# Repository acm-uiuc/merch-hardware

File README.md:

# Hardware to make Merch function

All the designs for the hardware components of Merch are found here.

## Components

### Vending Machine

This machine is a Dixie Narco 5800 Bevmax **4**, **not a Bevmax 3 machine**.

### Merch Hat

This unofficial Raspberry-Pi Hat allows a Pi to emulate keypresses on the machine's keypad.

### iPad Mount

### Connection Pictures

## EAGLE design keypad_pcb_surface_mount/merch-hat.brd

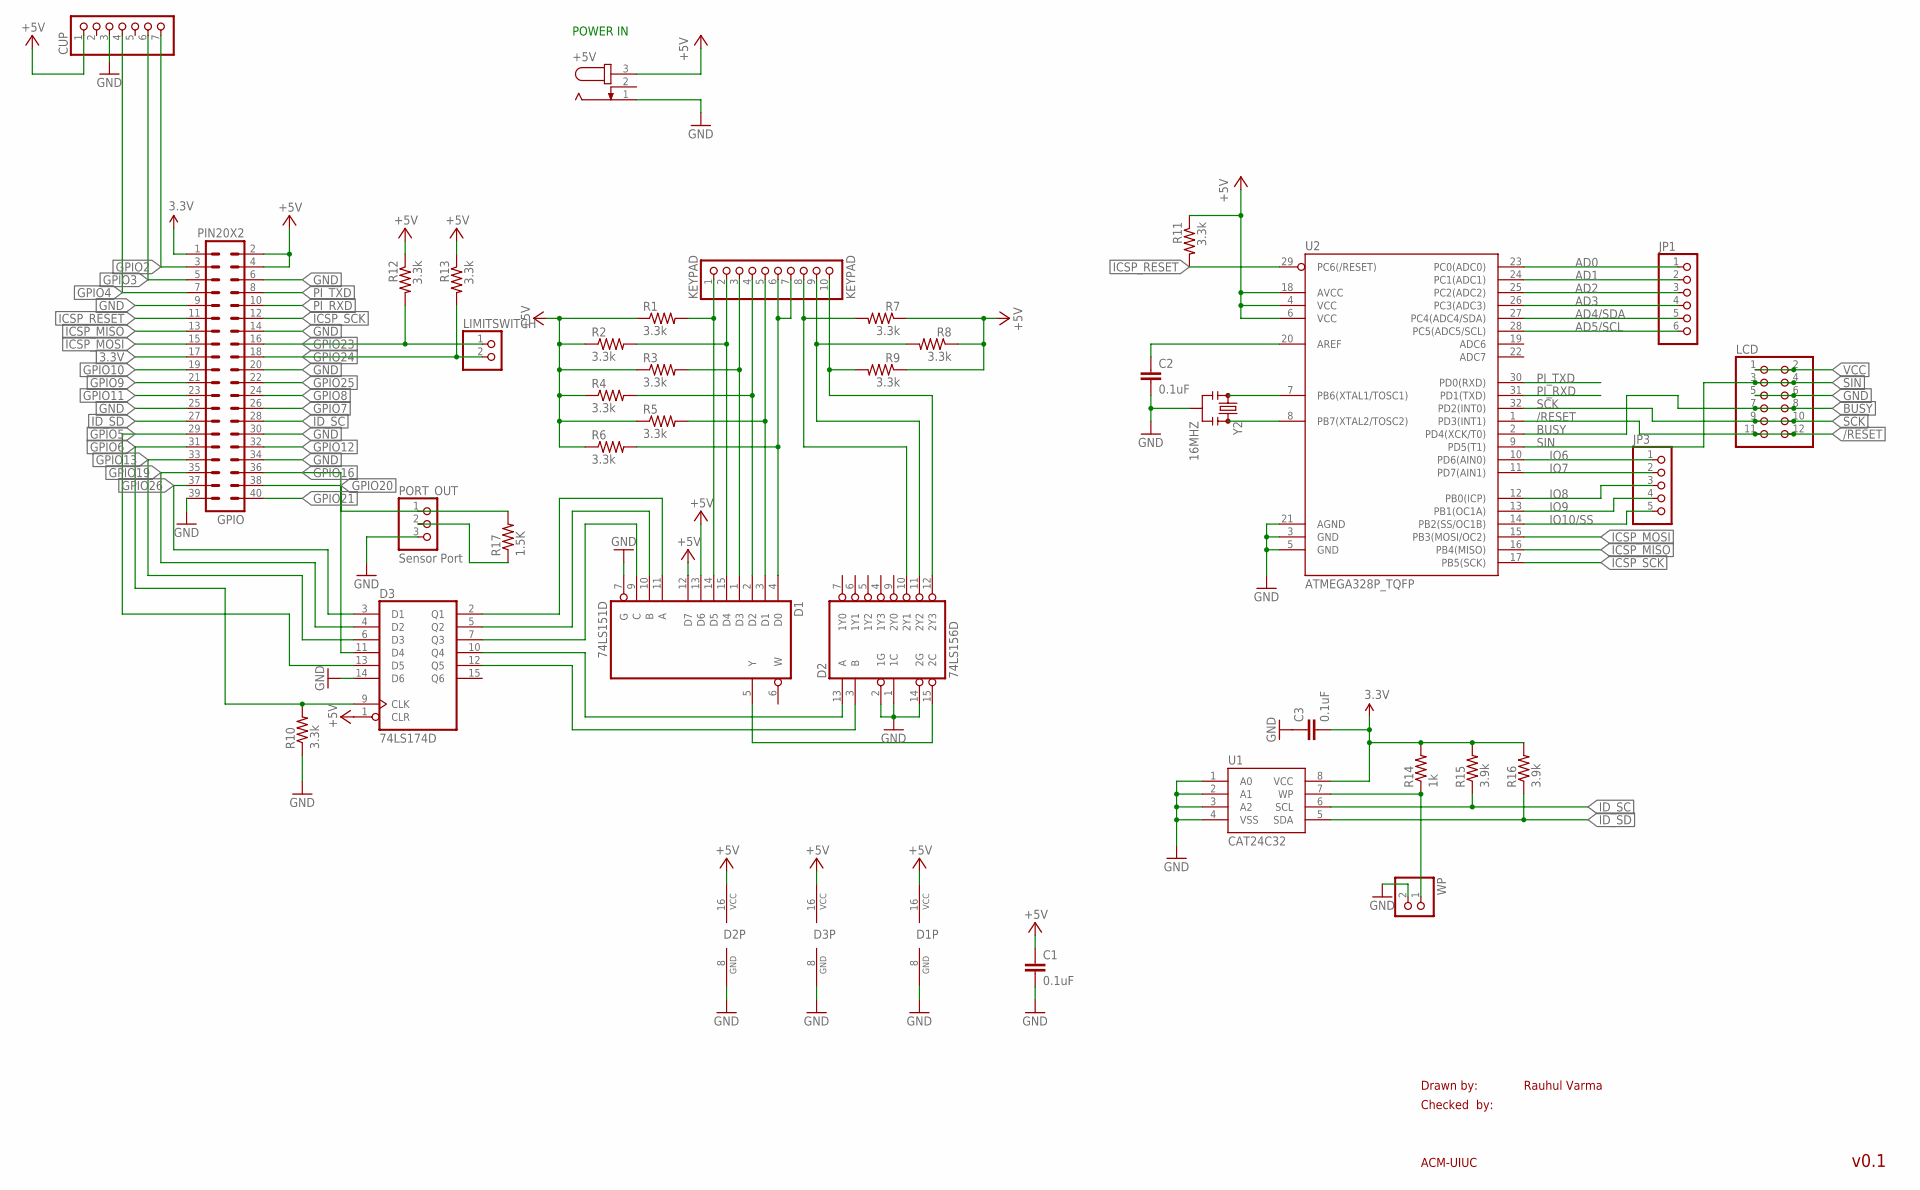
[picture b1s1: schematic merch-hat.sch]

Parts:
+5V: JACK-PLUG1; SPC4078
C1, C2, C3: 0.1uF; 0603-CAP
CUP: PINHD-1X7; 1X07
D1: 74LS151D; SO16
D2: 74LS156D; SO16
D3: 74LS174D; SO16
GPIO: PIN20X2; PIN_20X2
JP1: PINHD-1X6; 1X06
JP3: PINHD-1X5; 1X05
KEYPAD: KEYPAD; 1X10
LCD: PINHD-2X6; 2X06
LIMITSWITCH: PINHD-1X2; 1X02
PORT_OUT: Sensor Port; 1X03
R1, R2, R3, R4, R5, R6, R7, R8, R9, R10, R11, R12, R13: 3.3k; 0603-RES
R14: 1k; 0603-RES
R15, R16: 3.9k; 0603-RES
R17: 1.5K; R0603
U1: CAT24C32; SO08
U2: ATMEGA328P_TQFP; TQFP32-08
WP: PINHD-1X2; 1X02
Y2: 16MHZ; RESONATOR-SMD

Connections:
3.3V: C3.2, GPIO.1, GPIO.17, R14.2, R15.2, R16.2, U1.8 (VCC)
+5V: +5V.3, C1.1, CUP.1, D1.12 (D7), D1.13 (D6), D1.16 (VCC), D2.16 (VCC), D3.1 (CLR), D3.16 (VCC), GPIO.2, GPIO.4, R1.1, R2.1, R3.1, R4.1, R5.1, R6.1, R7.1, R8.1, R9.1, R11.1, R12.1, R13.1, U2.4 (VCC), U2.6 (VCC), U2.18 (AVCC)
/RESET: LCD.11, LCD.12, U2.1 (PD3(INT1))
AD0: JP1.1, U2.23 (PC0(ADC0))
AD1: JP1.2, U2.24 (PC1(ADC1))
AD2: JP1.3, U2.25 (PC2(ADC2))
AD3: JP1.4, U2.26 (PC3(ADC3))
AD4/SDA: JP1.5, U2.27 (PC4(ADC4/SDA))
AD5/SCL: JP1.6, U2.28 (PC5(ADC5/SCL))
BUSY: LCD.7, LCD.8, U2.2 (PD4(XCK/T0))
GND: +5V.1, C1.2, C2.2, C3.1, CUP.3, D1.7 (G), D1.8 (GND), D2.1 (1C), D2.2 (1G), D2.8 (GND), D2.14 (2G), D3.8 (GND), D3.14 (D6), GPIO.6, GPIO.9, GPIO.14, GPIO.20, GPIO.25, GPIO.30, GPIO.34, GPIO.39, LCD.5, LCD.6, PORT_OUT.3, R10.1, U1.1 (A0), U1.2 (A1), U1.3 (A2), U1.4 (VSS), U2.3 (GND), U2.5 (GND), U2.21 (AGND), WP.2, Y2.2
GPIO2: CUP.7, GPIO.3
GPIO3: CUP.6, GPIO.5
GPIO4: CUP.4, GPIO.7
GPIO5: D3.13 (D5), GPIO.29
GPIO6: D3.9 (CLK), GPIO.31, R10.2
GPIO7: GPIO.26
GPIO8: GPIO.24
GPIO9: GPIO.21
GPIO10: GPIO.19
GPIO11: GPIO.23
GPIO12: GPIO.32
GPIO13: D3.6 (D3), GPIO.33
GPIO16: D3.11 (D4), GPIO.36
GPIO19: D3.4 (D2), GPIO.35
GPIO20: GPIO.38, PORT_OUT.1, R17.2
GPIO21: GPIO.40
GPIO23: GPIO.16, LIMITSWITCH.1, R12.2
GPIO24: GPIO.18, LIMITSWITCH.2, R13.2
GPIO25: GPIO.22
GPIO26: D3.3 (D1), GPIO.37
ICSP_MISO: GPIO.13, U2.16 (PB4(MISO))
ICSP_MOSI: GPIO.15, U2.15 (PB3(MOSI/OC2))
ICSP_RESET: GPIO.11, R11.2, U2.29 (PC6(/RESET))
ICSP_SCK: GPIO.12, U2.17 (PB5(SCK))
ID_SC: GPIO.28, R15.1, U1.6 (SCL)
ID_SD: GPIO.27, R16.1, U1.5 (SDA)
IO6: JP3.1, U2.10 (PD6(AIN0))
IO7: JP3.2, U2.11 (PD7(AIN1))
IO8: JP3.3, U2.12 (PB0(ICP))
IO9: JP3.4, U2.13 (PB1(OC1A))
IO10/SS: JP3.5, U2.14 (PB2(SS/OC1B))
unnamed: D1.14 (D5), KEYPAD.1, R1.2
unnamed: R14.1, U1.7 (WP), WP.1
unnamed: PORT_OUT.2, R17.1
unnamed: D1.15 (D4), KEYPAD.2, R2.2
unnamed: D1.1 (D3), KEYPAD.3, R3.2
unnamed: D1.2 (D2), KEYPAD.4, R4.2
unnamed: D1.3 (D1), KEYPAD.5, R5.2
unnamed: D1.11 (A), D3.2 (Q1)
unnamed: D1.4 (D0), KEYPAD.6, KEYPAD.7, R6.2
unnamed: D2.10 (2Y1), KEYPAD.8, R7.2
unnamed: D2.11 (2Y2), KEYPAD.9, R8.2
unnamed: D2.12 (2Y3), KEYPAD.10, R9.2
unnamed: D1.10 (B), D3.5 (Q2)
unnamed: D1.9 (C), D3.7 (Q3)
unnamed: D2.13 (A), D3.10 (Q4)
unnamed: D2.3 (B), D3.12 (Q5)
unnamed: D1.5 (Y), D2.15 (2C)
unnamed: U2.7 (PB6(XTAL1/TOSC1)), Y2.1
unnamed: U2.8 (PB7(XTAL2/TOSC2)), Y2.3
unnamed: C2.1, U2.20 (AREF)
PI_RXD: GPIO.10, U2.31 (PD1(TXD))
PI_TXD: GPIO.8, U2.30 (PD0(RXD))
SCK: LCD.9, LCD.10, U2.32 (PD2(INT0))
SIN: LCD.3, LCD.4, U2.9 (PD5(T1))
VCC: LCD.1, LCD.2

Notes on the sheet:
Drawn by:
Checked by:
ACM-UIUC
Rauhul Varma
v0.1
POWER IN

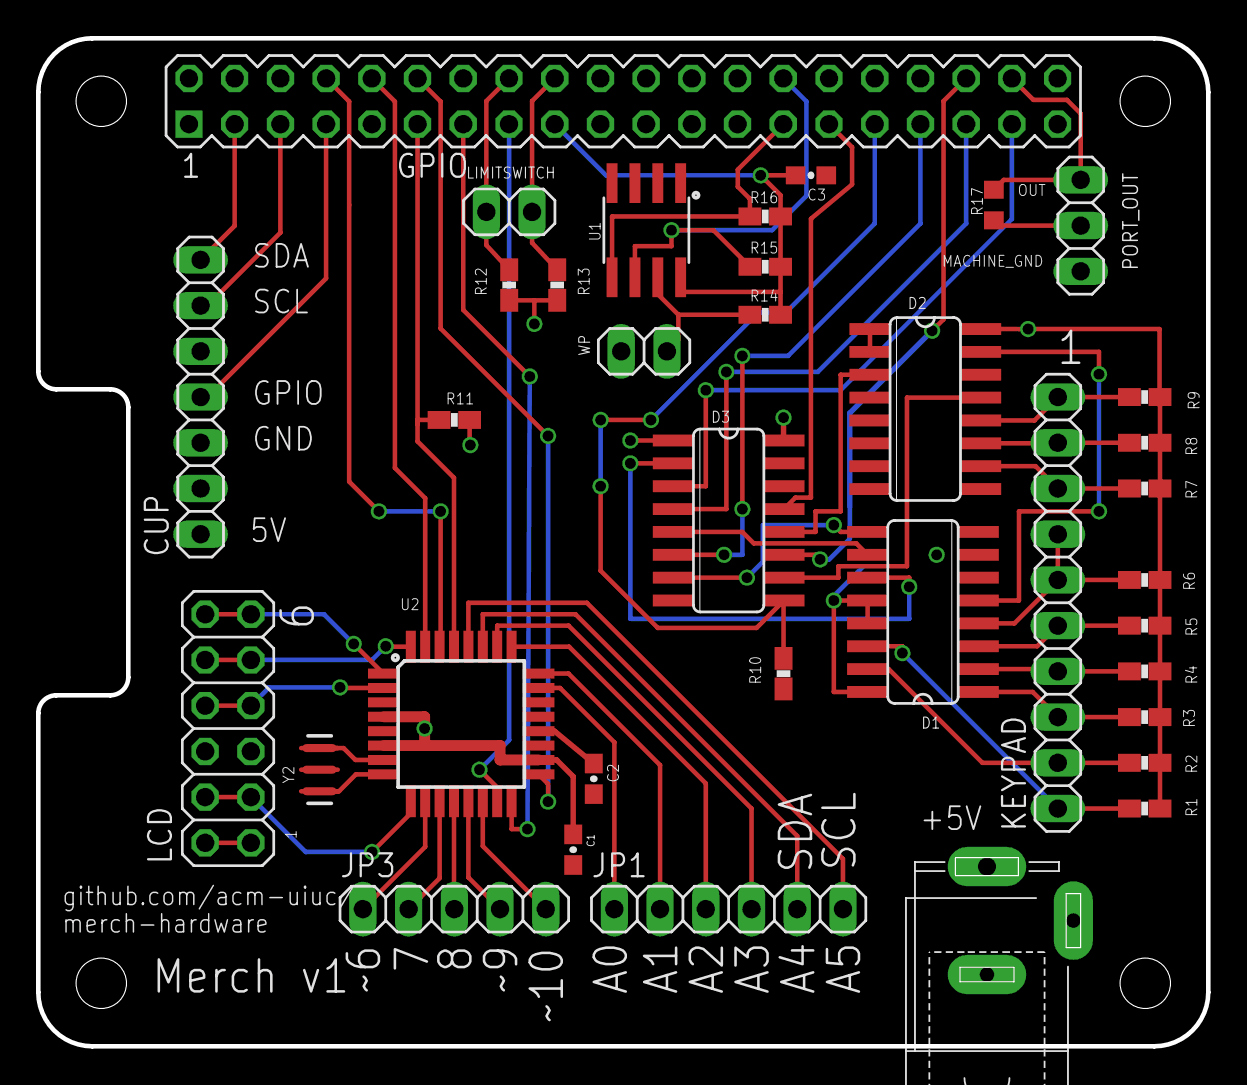
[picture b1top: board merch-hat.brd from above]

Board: 2 copper layers, 65.0 x 56.0 mm, 36 parts (0 on the bottom side), 59 nets.

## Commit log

2017-03-22 only hardware now
2017-04-10 Move Keypad, Add Port Sensor
2017-04-14 Finish Up Surface Mount Version
2017-04-14 add decoupling cap
2017-04-14 Add Limit Switch Interface
2017-04-14 Add Port Sensor Labels
2017-04-14 Minor fixes
2017-04-14 Add Custom port sensor mount
2017-04-14 Add gerber and dru files for seeedstudio
2017-04-17 Fixes and updates
2017-04-17 Change label, make vias circles
2017-04-19 Connect airwire
2017-04-19 Add png and github link
2017-04-21 fix misaligned routes, make all vias round, update board images
2017-09-03 Update LICENSE
2018-11-13 add power connctor, new range sensor pinout, pullup
2019-01-22 add pictures

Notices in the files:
parts and their libraries:
SparkFun-DigitalIC: Licensing: Creative Commons ShareAlike 4.0 International - https://creativecommons.org/licenses/by-sa/4.0
